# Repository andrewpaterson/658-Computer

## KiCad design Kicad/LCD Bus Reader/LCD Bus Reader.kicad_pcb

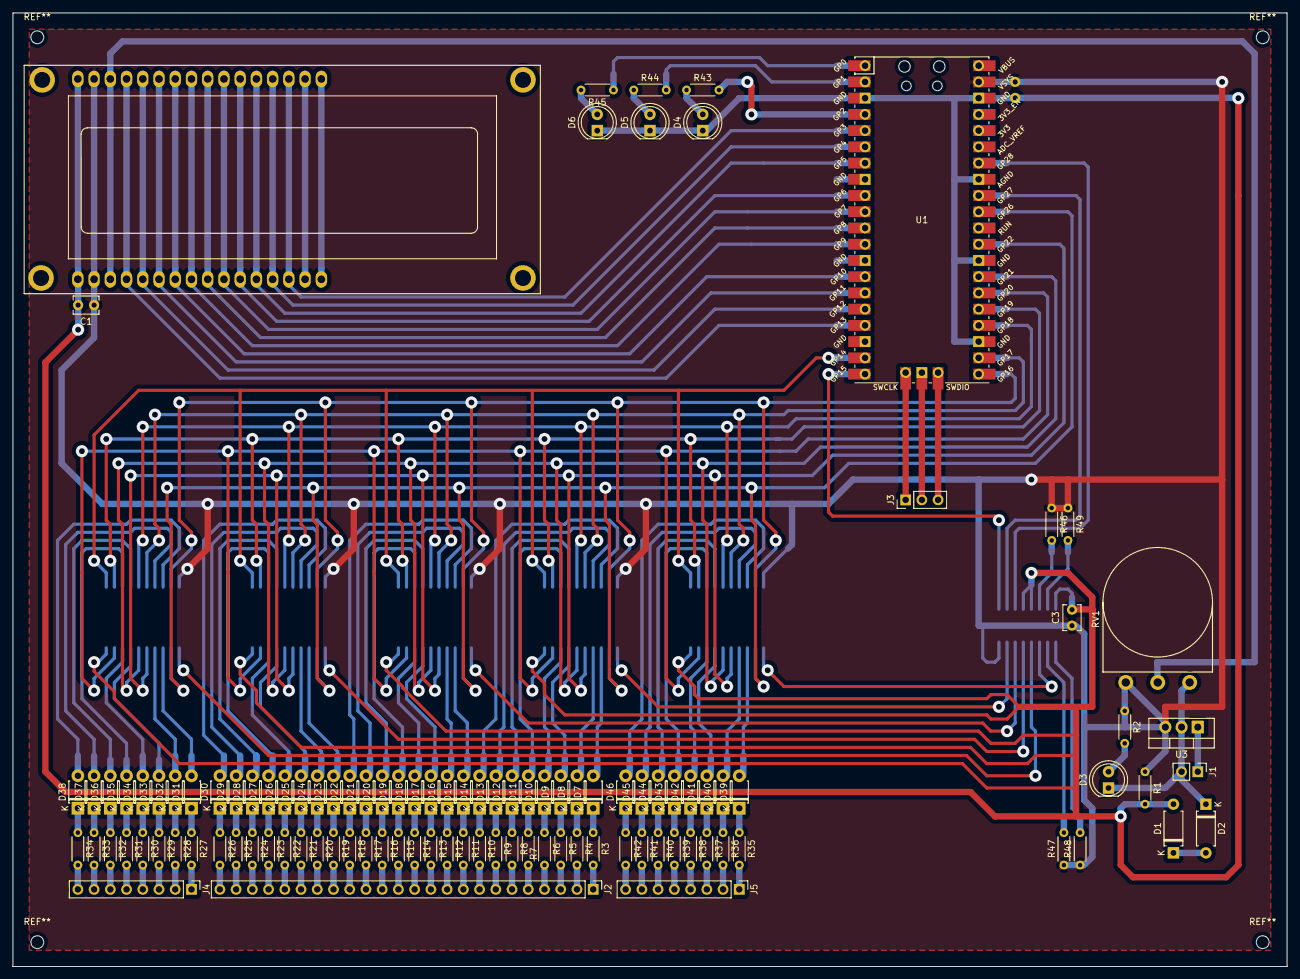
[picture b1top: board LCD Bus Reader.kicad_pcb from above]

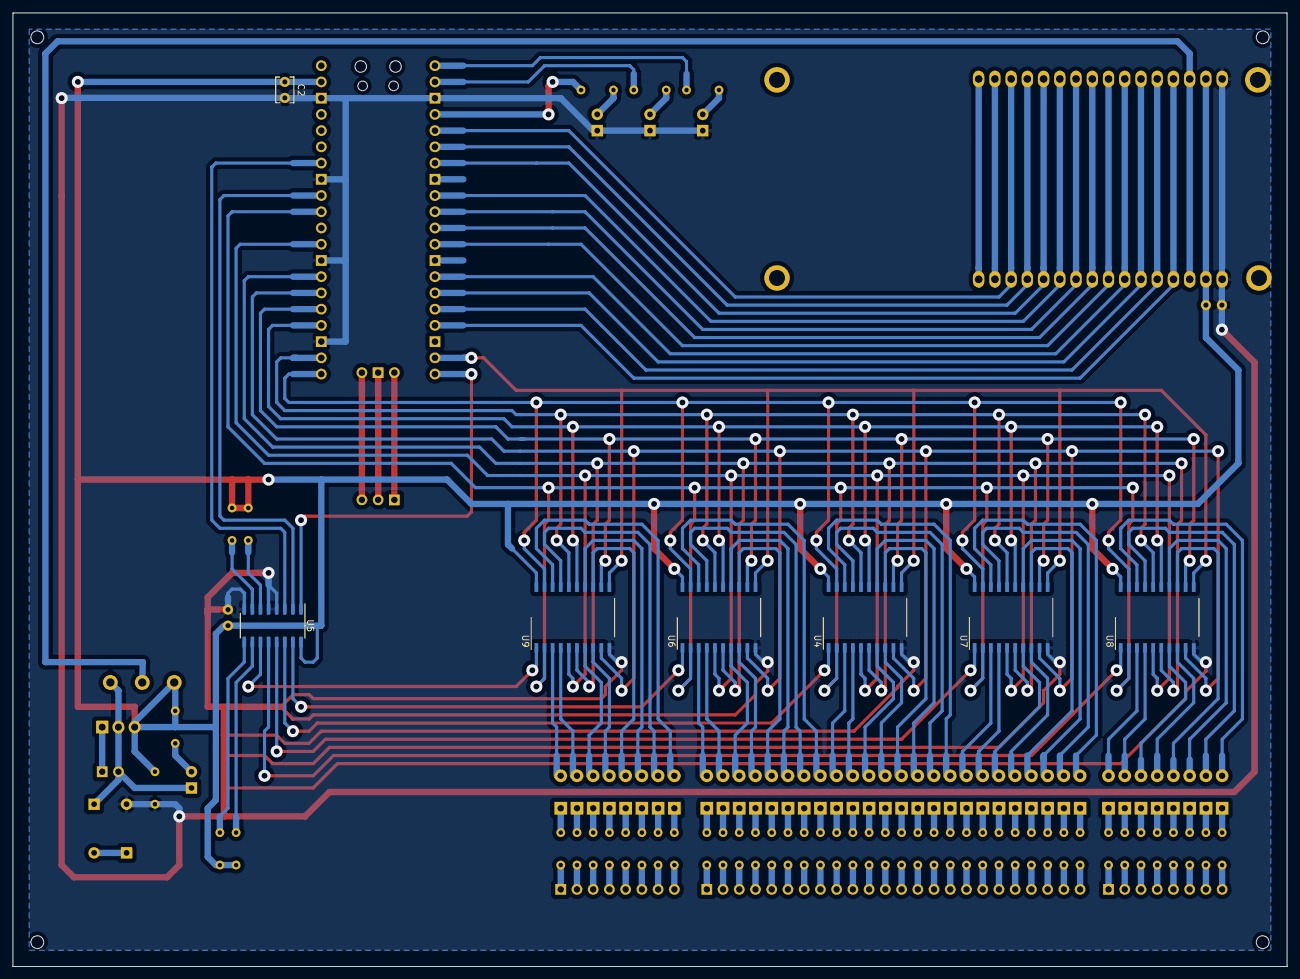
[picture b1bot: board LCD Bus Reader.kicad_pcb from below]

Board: 2 copper layers, 199.4 x 149.2 mm, 113 parts (7 on the bottom side), 168 nets.

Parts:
C1, C2, C3: C; C_Disc_D3.8mm_W2.6mm_P2.50mm
D1, D2: D_Zener; D_A-405_P7.62mm_Horizontal
D3, D4, D5, D6: LED; LED_D5.0mm
D7, D8, D9, D10, D11, D12, D13, D14, D15, D16, D17, D18, D19, D20, D21, D22, D23, D24, D25, D26, D27, D28, D29, D30, D31, D32, D33, D34, D35, D36, D37, D38, D39, D40, D41, D42, D43, D44, D45, D46: 1N4148; D_T-1_P5.08mm_Horizontal
J1: Conn_01x02_Male; PinHeader_1x02_P2.54mm_Vertical
J2: Conn_01x24_Male; PinHeader_1x24_P2.54mm_Vertical
J3: Conn_01x03_Male; PinHeader_1x03_P2.54mm_Vertical
J4, J5: Conn_01x08_Male; PinHeader_1x08_P2.54mm_Vertical
R1, R2, R3, R4, R5, R6, R7, R8, R9, R10, R11, R12, R13, R14, R15, R16, R17, R18, R19, R20, R21, R22, R23, R24, R25, R26, R27, R28, R29, R30, R31, R32, R33, R34, R35, R36, R37, R38, R39, R40, R41, R42, R43, R44, R45, R46, R47, R48, R49: R; R_Axial_DIN0204_L3.6mm_D1.6mm_P5.08mm_Horizontal
RV1: R_POT; Potentiometer_Omeg_PC16BU_Vertical
U1: Pico; RPi_Pico_SMD_TH
U2: RC1602A; NMTC-S16205
U3: L7805; TO-220-3_Vertical
U4, U6, U7, U8, U9: 74LS373; SO-20_12.8x7.5mm_P1.27mm
U5: 74LS138; SO-16_3.9x9.9mm_P1.27mm

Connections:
+12V: J1.1, U3.1
/0V: D2.1, D3.1, J1.2, RV1.1, U3.2
/1.6V: C1.2, C2.2, C3.2, D1.2, D4.1, D5.1, D6.1, R1.2, U1.3, U1.23, U1.28, U1.33, U1.38, U2.1, U4.10, U5.4, U5.5, U5.8, U6.10, U7.10, U8.10, U9.10
/5V: C1.1, C2.1, C3.1, R1.1, R2.1, R46.1, R47.1, R48.1, R49.1, RV1.3, U1.39, U2.2, U3.3, U4.20, U5.16, U6.20, U7.20, U8.20, U9.20
/CE0: U5.15, U6.1
/CE1: U4.1, U5.14
/CE2: U5.13, U7.1
/CE3: U5.12, U8.1
/CE4: U5.11, U9.1
/CE5: R47.2, U5.10
/CE6: R48.2, U5.9
/CE7: R49.2, U5.7
/CS0: U1.20, U5.1
/CS1: U1.32, U5.2
/CS2: U1.34, U5.3
/DB0: U1.14, U2.7
/DB1: U1.12, U2.8
/DB2: U1.11, U2.9
/DB3: U1.10, U2.10
/DB4: U1.9, U2.11
/DB5: U1.7, U2.12
/DB6: U1.6, U2.13
/DB7: U1.5, U2.14
/DET3: R46.2, U5.6
/E: U1.15, U2.6
/L0: U1.31, U4.2, U6.2, U7.2, U8.2, U9.2
/L1: U1.29, U4.5, U6.5, U7.5, U8.5, U9.5
/L2: U1.27, U4.6, U6.6, U7.6, U8.6, U9.6
/L3: U1.26, U4.9, U6.9, U7.9, U8.9, U9.9
/L4: U1.25, U4.12, U6.12, U7.12, U8.12, U9.12
/L5: U1.24, U4.15, U6.15, U7.15, U8.15, U9.15
/L6: U1.22, U4.16, U6.16, U7.16, U8.16, U9.16
/L7: U1.21, U4.19, U6.19, U7.19, U8.19, U9.19
/LE: U1.19, U4.11, U6.11, U7.11, U8.11, U9.11
/P1: D7.2, U6.3
/P2: D8.2, U6.4
/P3: D9.2, U6.7
/P4: D10.2, U6.8
/P5: D11.2, U6.13
/P6: D12.2, U6.14
/P7: D13.2, U6.17
/P8: D14.2, U6.18
/P9: D15.2, U4.3
/P10: D16.2, U4.4
/P11: D17.2, U4.7
/P12: D18.2, U4.8
/P13: D19.2, U4.13
/P14: D20.2, U4.14
/P15: D21.2, U4.17
/P16: D22.2, U4.18
/P17: D23.2, U7.3
/P18: D24.2, U7.4
/P19: D25.2, U7.7
/P20: D26.2, U7.8
/P21: D27.2, U7.13
/P22: D28.2, U7.14
/P23: D29.2, U7.17
/P24: D30.2, U7.18
/P25: D31.2, U8.3
/P26: D32.2, U8.4
/P27: D33.2, U8.7
/P28: D34.2, U8.8
/P29: D35.2, U8.13
/P30: D36.2, U8.14
/P31: D37.2, U8.17
/P32: D38.2, U8.18
/P33: D39.2, U9.3
/P34: D40.2, U9.4
/P35: D41.2, U9.7
/P36: D42.2, U9.8
/P37: D43.2, U9.13
/P38: D44.2, U9.14
/P39: D45.2, U9.17
/P40: D46.2, U9.18
/RS: U1.17, U2.4
/RW: U1.16, U2.5
/V0: RV1.2, U2.3
unnamed: D1.1, D2.2
unnamed: D3.2, R2.2
unnamed: D4.2, R43.1
unnamed: D5.2, R44.1
unnamed: D6.2, R45.2
unnamed: D7.1, R3.1
unnamed: D8.1, R4.1
unnamed: D9.1, R5.1
unnamed: D10.1, R6.1
unnamed: D11.1, R7.1
unnamed: D12.1, R8.1
unnamed: D13.1, R9.1
unnamed: D14.1, R10.1
unnamed: D15.1, R11.1
unnamed: D16.1, R12.1
unnamed: D17.1, R13.1
unnamed: D18.1, R14.1
unnamed: D19.1, R15.1
unnamed: D20.1, R16.1
unnamed: D21.1, R17.1
unnamed: D22.1, R18.1
unnamed: D23.1, R19.1
unnamed: D24.1, R20.1
unnamed: D25.1, R21.1
unnamed: D26.1, R22.1
unnamed: D27.1, R23.1
unnamed: D28.1, R24.1
unnamed: D29.1, R25.1
unnamed: D30.1, R26.1
unnamed: D31.1, R27.1
unnamed: D32.1, R28.1
unnamed: D33.1, R29.1
unnamed: D34.1, R30.1
unnamed: D35.1, R31.1
unnamed: D36.1, R32.1
unnamed: D37.1, R33.1
unnamed: D38.1, R34.1
unnamed: D39.1, R35.1
unnamed: D40.1, R36.1
unnamed: D41.1, R37.1
unnamed: D42.1, R38.1
unnamed: D43.1, R39.1
unnamed: D44.1, R40.1
unnamed: D45.1, R41.1
unnamed: D46.1, R42.1
unnamed: J2.1, R3.2
unnamed: J2.2, R4.2
unnamed: J2.3, R5.2
unnamed: J2.4, R6.2
unnamed: J2.5, R7.2
unnamed: J2.6, R8.2
unnamed: J2.7, R9.2
unnamed: J2.8, R10.2
unnamed: J2.9, R11.2
unnamed: J2.10, R12.2
unnamed: J2.11, R13.2
unnamed: J2.12, R14.2
unnamed: J2.13, R15.2
unnamed: J2.14, R16.2
unnamed: J2.15, R17.2
unnamed: J2.16, R18.2
unnamed: J2.17, R19.2
unnamed: J2.18, R20.2
unnamed: J2.19, R21.2
unnamed: J2.20, R22.2
unnamed: J2.21, R23.2
unnamed: J2.22, R24.2
unnamed: J2.23, R25.2
unnamed: J2.24, R26.2
unnamed: J3.1, U1.41
unnamed: J3.2, U1.42
unnamed: J3.3, U1.43
unnamed: J4.1, R27.2
unnamed: J4.2, R28.2
unnamed: J4.3, R29.2
unnamed: J4.4, R30.2
unnamed: J4.5, R31.2
unnamed: J4.6, R32.2
unnamed: J4.7, R33.2
unnamed: J4.8, R34.2
unnamed: J5.1, R35.2
unnamed: J5.2, R36.2
unnamed: J5.3, R37.2
unnamed: J5.4, R38.2
unnamed: J5.5, R39.2
unnamed: J5.6, R40.2
unnamed: J5.7, R41.2
unnamed: J5.8, R42.2
unnamed: R43.2, U1.4
unnamed: R44.2, U1.2
unnamed: R45.1, U1.1

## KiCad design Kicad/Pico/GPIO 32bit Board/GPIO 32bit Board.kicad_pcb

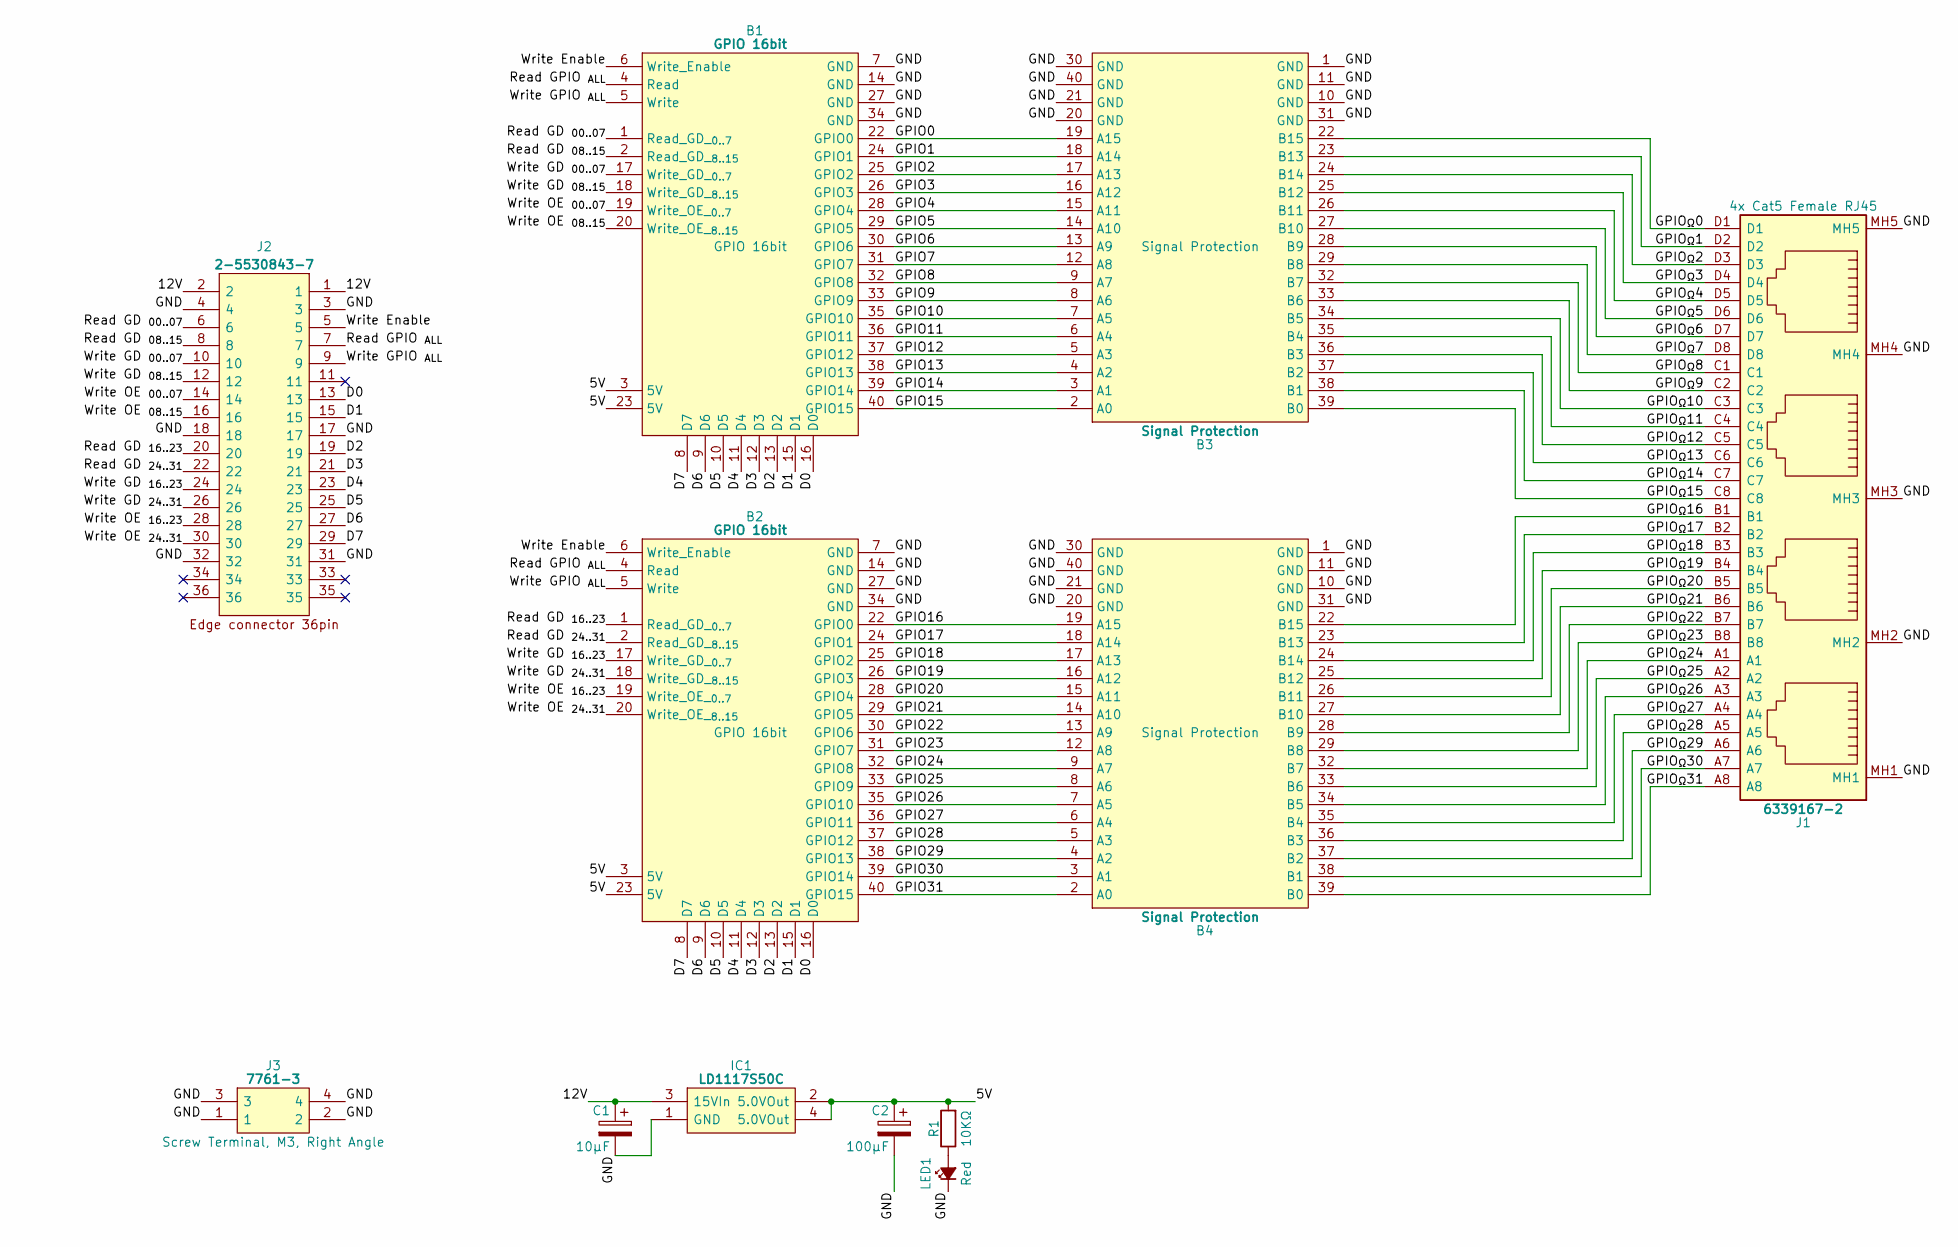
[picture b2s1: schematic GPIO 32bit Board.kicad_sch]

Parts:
B1, B2: GPIO 16bit; HCP65_GPIO_16bit
B3, B4: Signal Protection; HCP65_Signal_Protection
C1: 10μF; CP_Radial_D4.0mm_P2.00mm
C2: 100μF; CP_Radial_D4.0mm_P2.00mm
IC1: LD1117S50C; LD1117S33C; Manufacturer_Part_Number LD1117S50C
J1: 6339167-2; 63391672; Manufacturer_Part_Number 6339167-2; Mouser Part Number 571-6339167-2
J2: 2-5530843-7; 36pin Edge Connector; Manufacturer_Part_Number 2-5530843-7; Mouser Part Number 571-2-5530843-7
J3: 7761-3; 77613; Manufacturer_Part_Number 7761-3
LED1: Red; LED_D5.0mm
R1: 10KΩ; R_Axial_DIN0204_L3.6mm_D1.6mm_P5.08mm_Horizontal

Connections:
/5V: B1.3 (5V), B1.23 (5V), B2.3 (5V), B2.23 (5V), C2.1, IC1.2 (5.0VOut), IC1.4 (5.0VOut), R1.2
/12V: C1.1, IC1.3 (15VIn), J2.1, J2.2
/D0: B1.16 (D0), B2.16 (D0), J2.13
/D1: B1.15 (D1), B2.15 (D1), J2.15
/D2: B1.13 (D2), B2.13 (D2), J2.19
/D3: B1.12 (D3), B2.12 (D3), J2.21
/D4: B1.11 (D4), B2.11 (D4), J2.23
/D5: B1.10 (D5), B2.10 (D5), J2.25
/D6: B1.9 (D6), B2.9 (D6), J2.27
/D7: B1.8 (D7), B2.8 (D7), J2.29
/GND: B1.7 (GND), B1.14 (GND), B1.27 (GND), B1.34 (GND), B2.7 (GND), B2.14 (GND), B2.27 (GND), B2.34 (GND), B3.1 (GND), B3.10 (GND), B3.11 (GND), B3.20 (GND), B3.21 (GND), B3.30 (GND), B3.31 (GND), B3.40 (GND), B4.1 (GND), B4.10 (GND), B4.11 (GND), B4.20 (GND), B4.21 (GND), B4.30 (GND), B4.31 (GND), B4.40 (GND), C1.2, C2.2, IC1.1 (GND), J1.MH1, J1.MH2, J1.MH3, J1.MH4, J1.MH5, J2.3, J2.4, J2.17, J2.18, J2.31, J2.32, J3.1, J3.2, J3.3, J3.4, LED1.1 (K)
/GPIO0: B1.22 (GPIO0), B3.19 (A15)
/GPIO1: B1.24 (GPIO1), B3.18 (A14)
/GPIO2: B1.25 (GPIO2), B3.17 (A13)
/GPIO3: B1.26 (GPIO3), B3.16 (A12)
/GPIO4: B1.28 (GPIO4), B3.15 (A11)
/GPIO5: B1.29 (GPIO5), B3.14 (A10)
/GPIO6: B1.30 (GPIO6), B3.13 (A9)
/GPIO7: B1.31 (GPIO7), B3.12 (A8)
/GPIO8: B1.32 (GPIO8), B3.9 (A7)
/GPIO9: B1.33 (GPIO9), B3.8 (A6)
/GPIO10: B1.35 (GPIO10), B3.7 (A5)
/GPIO11: B1.36 (GPIO11), B3.6 (A4)
/GPIO12: B1.37 (GPIO12), B3.5 (A3)
/GPIO13: B1.38 (GPIO13), B3.4 (A2)
/GPIO14: B1.39 (GPIO14), B3.3 (A1)
/GPIO15: B1.40 (GPIO15), B3.2 (A0)
/GPIO16: B2.22 (GPIO0), B4.19 (A15)
/GPIO17: B2.24 (GPIO1), B4.18 (A14)
/GPIO18: B2.25 (GPIO2), B4.17 (A13)
/GPIO19: B2.26 (GPIO3), B4.16 (A12)
/GPIO20: B2.28 (GPIO4), B4.15 (A11)
/GPIO21: B2.29 (GPIO5), B4.14 (A10)
/GPIO22: B2.30 (GPIO6), B4.13 (A9)
/GPIO23: B2.31 (GPIO7), B4.12 (A8)
/GPIO24: B2.32 (GPIO8), B4.9 (A7)
/GPIO25: B2.33 (GPIO9), B4.8 (A6)
/GPIO26: B2.35 (GPIO10), B4.7 (A5)
/GPIO27: B2.36 (GPIO11), B4.6 (A4)
/GPIO28: B2.37 (GPIO12), B4.5 (A3)
/GPIO29: B2.38 (GPIO13), B4.4 (A2)
/GPIO30: B2.39 (GPIO14), B4.3 (A1)
/GPIO31: B2.40 (GPIO15), B4.2 (A0)
/GPIO_{Ω}0: B3.22 (B15), J1.D1
/GPIO_{Ω}1: B3.23 (B13), J1.D2
/GPIO_{Ω}2: B3.24 (B14), J1.D3
/GPIO_{Ω}3: B3.25 (B12), J1.D4
/GPIO_{Ω}4: B3.26 (B11), J1.D5
/GPIO_{Ω}5: B3.27 (B10), J1.D6
/GPIO_{Ω}6: B3.28 (B9), J1.D7
/GPIO_{Ω}7: B3.29 (B8), J1.D8
/GPIO_{Ω}8: B3.32 (B7), J1.C1
/GPIO_{Ω}9: B3.33 (B6), J1.C2
/GPIO_{Ω}10: B3.34 (B5), J1.C3
/GPIO_{Ω}11: B3.35 (B4), J1.C4
/GPIO_{Ω}12: B3.36 (B3), J1.C5
/GPIO_{Ω}13: B3.37 (B2), J1.C6
/GPIO_{Ω}14: B3.38 (B1), J1.C7
/GPIO_{Ω}15: B3.39 (B0), J1.C8
/GPIO_{Ω}16: B4.22 (B15), J1.B1
/GPIO_{Ω}17: B4.23 (B13), J1.B2
/GPIO_{Ω}18: B4.24 (B14), J1.B3
/GPIO_{Ω}19: B4.25 (B12), J1.B4
/GPIO_{Ω}20: B4.26 (B11), J1.B5
/GPIO_{Ω}21: B4.27 (B10), J1.B6
/GPIO_{Ω}22: B4.28 (B9), J1.B7
/GPIO_{Ω}23: B4.29 (B8), J1.B8
/GPIO_{Ω}24: B4.32 (B7), J1.A1
/GPIO_{Ω}25: B4.33 (B6), J1.A2
/GPIO_{Ω}26: B4.34 (B5), J1.A3
/GPIO_{Ω}27: B4.35 (B4), J1.A4
/GPIO_{Ω}28: B4.36 (B3), J1.A5
/GPIO_{Ω}29: B4.37 (B2), J1.A6
/GPIO_{Ω}30: B4.38 (B1), J1.A7
/GPIO_{Ω}31: B4.39 (B0), J1.A8
/Read GD _{00..07}: B1.1 (Read_GD__{0..7}), J2.6
/Read GD _{08..15}: B1.2 (Read_GD__{8..15}), J2.8
/Read GD _{16..23}: B2.1 (Read_GD__{0..7}), J2.20
/Read GD _{24..31}: B2.2 (Read_GD__{8..15}), J2.22
/Read GPIO _{ALL}: B1.4 (Read), B2.4 (Read), J2.7
/Write Enable: B1.6 (Write_Enable), B2.6 (Write_Enable), J2.5
/Write GD _{00..07}: B1.17 (Write_GD__{0..7}), J2.10
/Write GD _{08..15}: B1.18 (Write_GD__{8..15}), J2.12
/Write GD _{16..23}: B2.17 (Write_GD__{0..7}), J2.24
/Write GD _{24..31}: B2.18 (Write_GD__{8..15}), J2.26
/Write GPIO _{ALL}: B1.5 (Write), B2.5 (Write), J2.9
/Write OE _{00..07}: B1.19 (Write_OE__{0..7}), J2.14
/Write OE _{08..15}: B1.20 (Write_OE__{8..15}), J2.16
/Write OE _{16..23}: B2.19 (Write_OE__{0..7}), J2.28
/Write OE _{24..31}: B2.20 (Write_OE__{8..15}), J2.30
unnamed: LED1.2 (A), R1.1

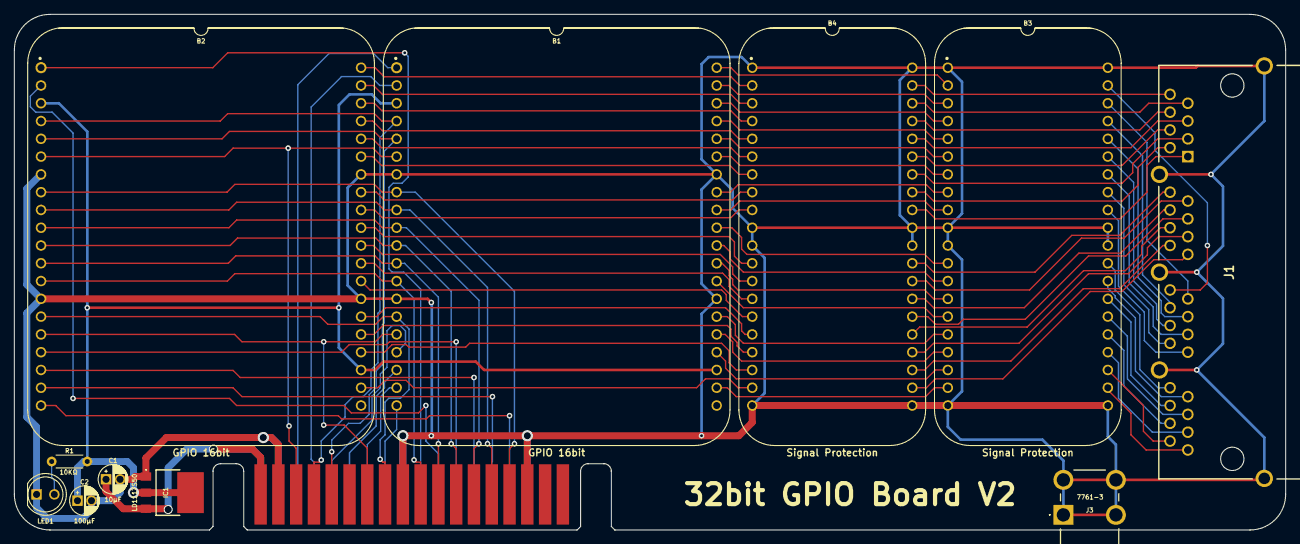
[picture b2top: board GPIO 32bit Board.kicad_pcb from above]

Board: 2 copper layers, 181.6 x 73.7 mm, 12 parts (0 on the bottom side), 91 nets.

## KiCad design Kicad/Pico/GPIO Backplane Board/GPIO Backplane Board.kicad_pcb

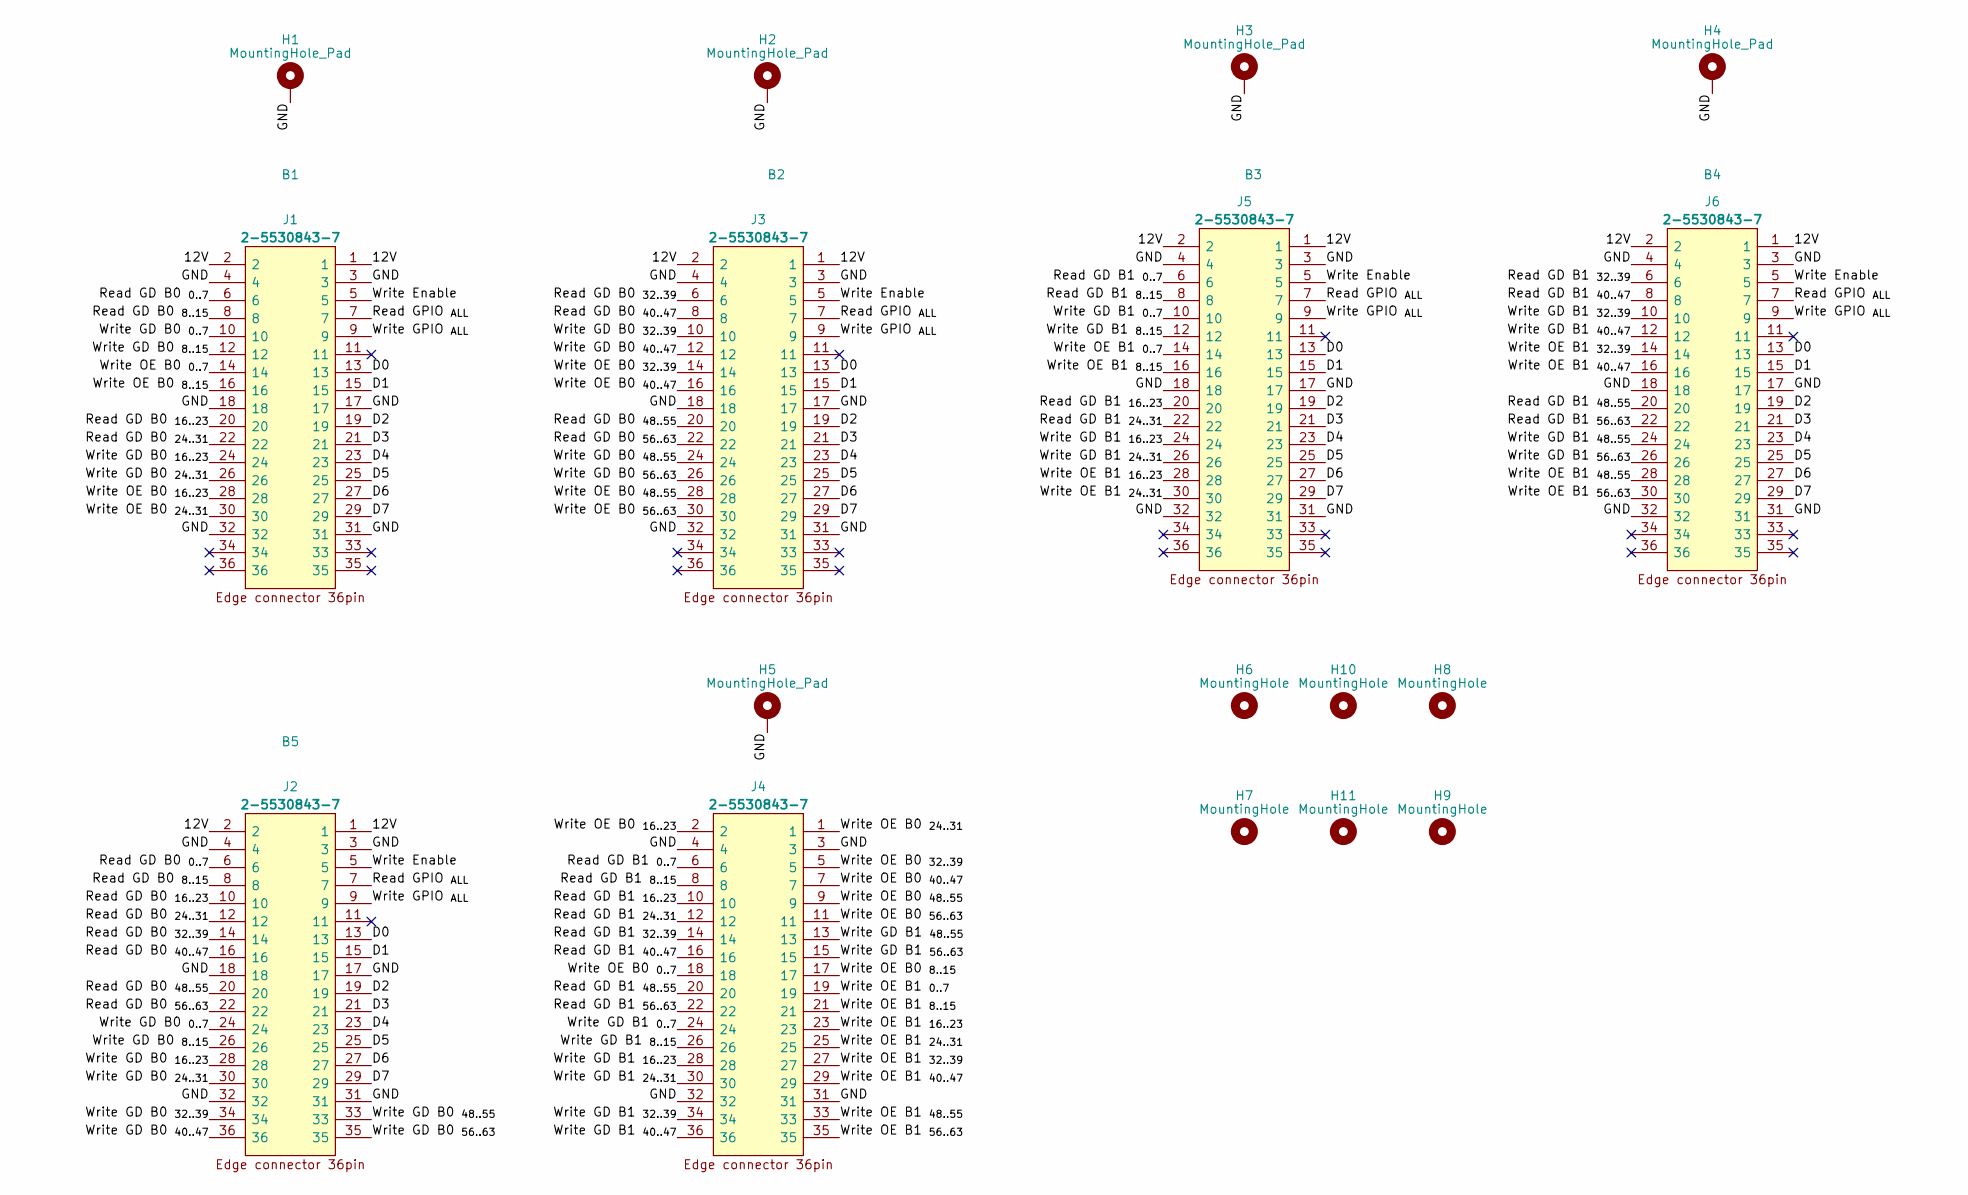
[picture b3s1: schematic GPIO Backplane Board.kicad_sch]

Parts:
B1, B2, B3, B4: HCP65_GPIO_32bit_Board
B5: HCP65_GPIO_Controller_Board
H1, H2, H3, H4, H5: MountingHole_Pad; MountingHole_3.2mm_M3_Pad
H6, H7, H8, H9, H10, H11: MountingHole; MountingHole_3.2mm_M3
J1, J2, J3, J4, J5, J6: 2-5530843-7; 255308437; Manufacturer_Part_Number 2-5530843-7; Mouser Part Number 571-2-5530843-7

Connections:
/12V: J1.1, J1.2, J2.1, J2.2, J3.1, J3.2, J5.1, J5.2, J6.1, J6.2
/D0: J1.13, J2.13, J3.13, J5.13, J6.13
/D1: J1.15, J2.15, J3.15, J5.15, J6.15
/D2: J1.19, J2.19, J3.19, J5.19, J6.19
/D3: J1.21, J2.21, J3.21, J5.21, J6.21
/D4: J1.23, J2.23, J3.23, J5.23, J6.23
/D5: J1.25, J2.25, J3.25, J5.25, J6.25
/D6: J1.27, J2.27, J3.27, J5.27, J6.27
/D7: J1.29, J2.29, J3.29, J5.29, J6.29
/GND: H1.1, H2.1, H3.1, H4.1, H5.1, J1.3, J1.4, J1.17, J1.18, J1.31, J1.32, J2.3, J2.4, J2.17, J2.18, J2.31, J2.32, J3.3, J3.4, J3.17, J3.18, J3.31, J3.32, J4.3, J4.4, J4.31, J4.32, J5.3, J5.4, J5.17, J5.18, J5.31, J5.32, J6.3, J6.4, J6.17, J6.18, J6.31, J6.32
/Read GD B0 _{0..7}: J1.6, J2.6
/Read GD B0 _{8..15}: J1.8, J2.8
/Read GD B0 _{16..23}: J1.20, J2.10
/Read GD B0 _{24..31}: J1.22, J2.12
/Read GD B0 _{32..39}: J2.14, J3.6
/Read GD B0 _{40..47}: J2.16, J3.8
/Read GD B0 _{48..55}: J2.20, J3.20
/Read GD B0 _{56..63}: J2.22, J3.22
/Read GD B1 _{0..7}: J4.6, J5.6
/Read GD B1 _{8..15}: J4.8, J5.8
/Read GD B1 _{16..23}: J4.10, J5.20
/Read GD B1 _{24..31}: J4.12, J5.22
/Read GD B1 _{32..39}: J4.14, J6.6
/Read GD B1 _{40..47}: J4.16, J6.8
/Read GD B1 _{48..55}: J4.20, J6.20
/Read GD B1 _{56..63}: J4.22, J6.22
/Read GPIO _{ALL}: J1.7, J2.7, J3.7, J5.7, J6.7
/Write Enable: J1.5, J2.5, J3.5, J5.5, J6.5
/Write GD B0 _{0..7}: J1.10, J2.24
/Write GD B0 _{8..15}: J1.12, J2.26
/Write GD B0 _{16..23}: J1.24, J2.28
/Write GD B0 _{24..31}: J1.26, J2.30
/Write GD B0 _{32..39}: J2.34, J3.10
/Write GD B0 _{40..47}: J2.36, J3.12
/Write GD B0 _{48..55}: J2.33, J3.24
/Write GD B0 _{56..63}: J2.35, J3.26
/Write GD B1 _{0..7}: J4.24, J5.10
/Write GD B1 _{8..15}: J4.26, J5.12
/Write GD B1 _{16..23}: J4.28, J5.24
/Write GD B1 _{24..31}: J4.30, J5.26
/Write GD B1 _{32..39}: J4.34, J6.10
/Write GD B1 _{40..47}: J4.36, J6.12
/Write GD B1 _{48..55}: J4.13, J6.24
/Write GD B1 _{56..63}: J4.15, J6.26
/Write GPIO _{ALL}: J1.9, J2.9, J3.9, J5.9, J6.9
/Write OE B0 _{0..7}: J1.14, J4.18
/Write OE B0 _{8..15}: J1.16, J4.17
/Write OE B0 _{16..23}: J1.28, J4.2
/Write OE B0 _{24..31}: J1.30, J4.1
/Write OE B0 _{32..39}: J3.14, J4.5
/Write OE B0 _{40..47}: J3.16, J4.7
/Write OE B0 _{48..55}: J3.28, J4.9
/Write OE B0 _{56..63}: J3.30, J4.11
/Write OE B1 _{0..7}: J4.19, J5.14
/Write OE B1 _{8..15}: J4.21, J5.16
/Write OE B1 _{16..23}: J4.23, J5.28
/Write OE B1 _{24..31}: J4.25, J5.30
/Write OE B1 _{32..39}: J4.27, J6.14
/Write OE B1 _{40..47}: J4.29, J6.16
/Write OE B1 _{48..55}: J4.33, J6.28
/Write OE B1 _{56..63}: J4.35, J6.30

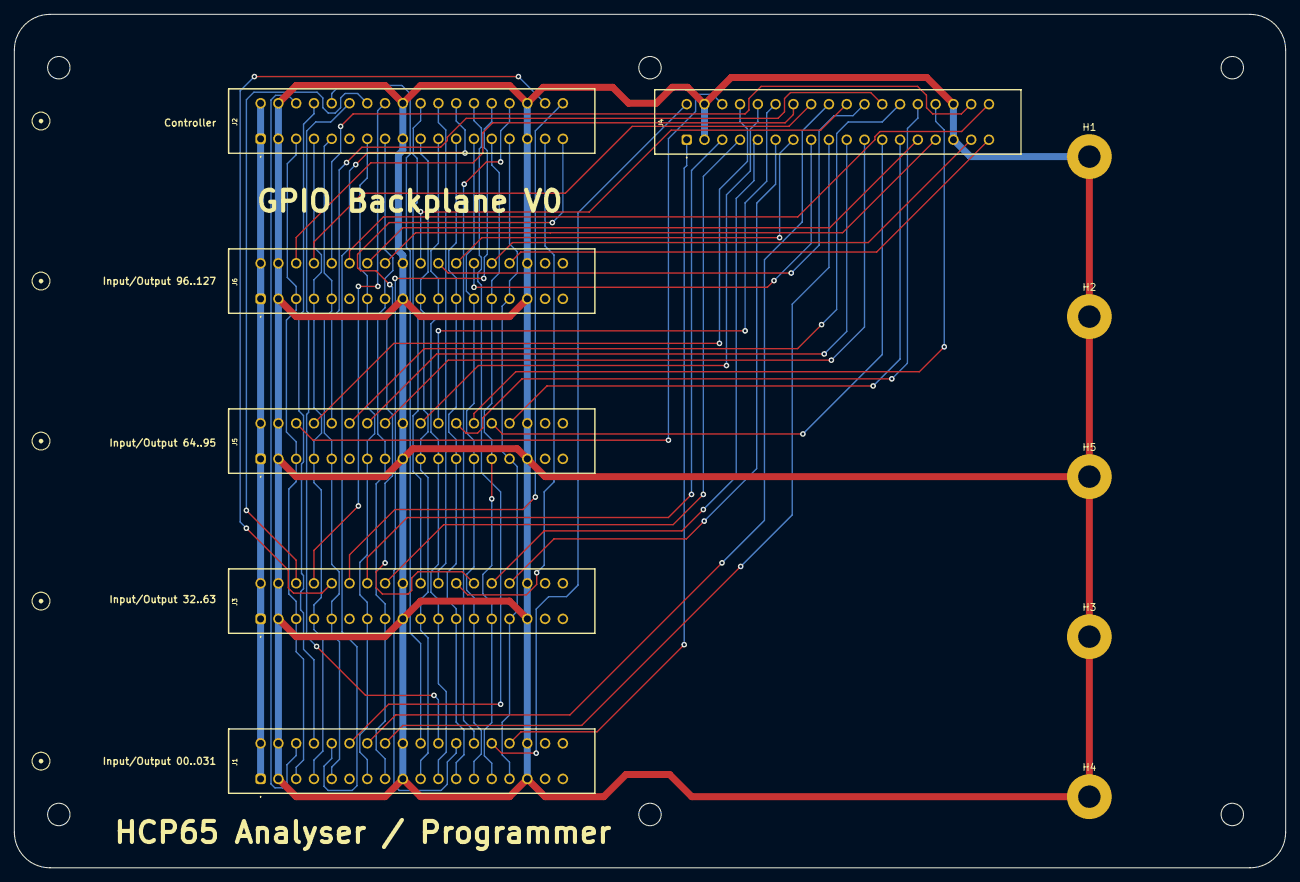
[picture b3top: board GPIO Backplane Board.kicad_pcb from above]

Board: 2 copper layers, 181.6 x 121.9 mm, 22 parts (0 on the bottom side), 61 nets.

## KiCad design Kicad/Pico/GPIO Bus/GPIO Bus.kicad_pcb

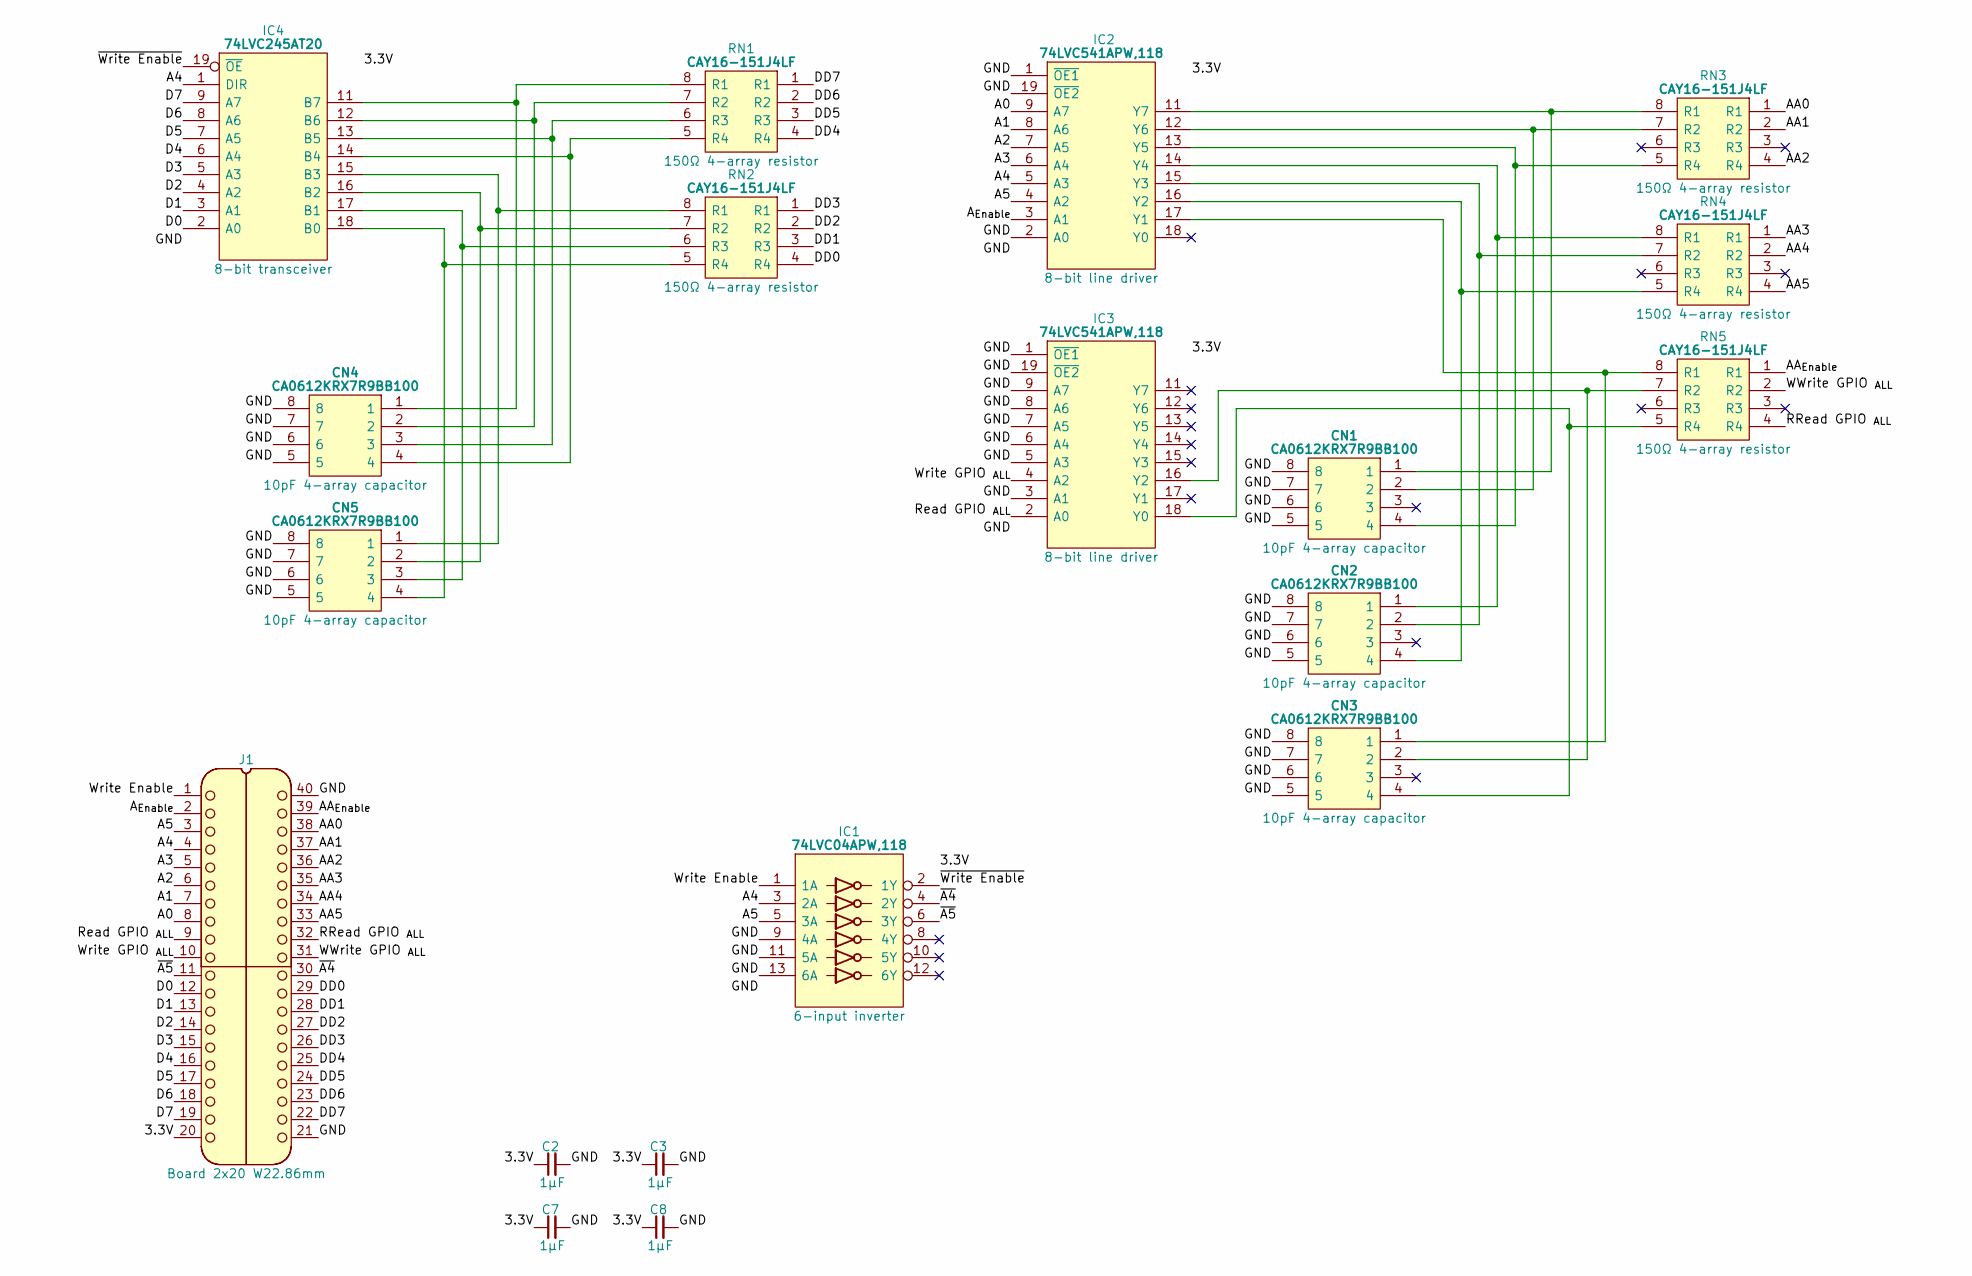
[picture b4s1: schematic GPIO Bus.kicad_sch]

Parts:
C2, C3, C7, C8: 1μF; C_0805
CN1, CN2, CN3, CN4, CN5: CA0612KRX7R9BB100; Manufacturer_Part_Number CA0612KRX7R9BB102; Mouser Part Number 603-CA612KRX7R9BB102
IC1: 74LVC04APW,118; SOP65P640X110-14N; Manufacturer_Part_Number 74LVC04APW,118; Mouser Part Number 771-74LVC04APW-T
IC2, IC3: 74LVC541APW,118; SOP65P640X110-20N; Mouser Part Number 771-74LVC541APW-T
IC4: 74LVC245AT20; SOP65P640X120-20N; Manufacturer_Part_Number 74LVC245AT20-13; Mouser Part Number 621-74LVC245AT20-13
J1: Board 2x20 W22.86mm; DIP-40_Board_W22.86mm
RN1, RN2, RN3, RN4, RN5: CAY16-151J4LF; CAY16-J4; Manufacturer_Part_Number CAY16-151J4LF; Mouser Part Number 652-CAY16-151J4LF

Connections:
/3.3V: C2.1, C3.1, C7.1, C8.1, IC1.14 (3V), IC2.20 (3V), IC3.20 (3V), IC4.20 (3V), J1.20
/A0: IC2.9 (A7), J1.8
/A1: IC2.8 (A6), J1.7
/A2: IC2.7 (A5), J1.6
/A3: IC2.6 (A4), J1.5
/A4: IC1.3 (2A), IC2.5 (A3), IC4.1 (DIR), J1.4
/A5: IC1.5 (3A), IC2.4 (A2), J1.3
/AA0: J1.38, RN3.1 (R1)
/AA1: J1.37, RN3.2 (R2)
/AA2: J1.36, RN3.4 (R4)
/AA3: J1.35, RN4.1 (R1)
/AA4: J1.34, RN4.2 (R2)
/AA5: J1.33, RN4.4 (R4)
/AA_{Enable}: J1.39, RN5.1 (R1)
/A_{Enable}: IC2.3 (A1), J1.2
/D0: IC4.2 (A0), J1.12
/D1: IC4.3 (A1), J1.13
/D2: IC4.4 (A2), J1.14
/D3: IC4.5 (A3), J1.15
/D4: IC4.6 (A4), J1.16
/D5: IC4.7 (A5), J1.17
/D6: IC4.8 (A6), J1.18
/D7: IC4.9 (A7), J1.19
/DD0: J1.29, RN2.4 (R4)
/DD1: J1.28, RN2.3 (R3)
/DD2: J1.27, RN2.2 (R2)
/DD3: J1.26, RN2.1 (R1)
/DD4: J1.25, RN1.4 (R4)
/DD5: J1.24, RN1.3 (R3)
/DD6: J1.23, RN1.2 (R2)
/DD7: J1.22, RN1.1 (R1)
/GND: C2.2, C3.2, C7.2, C8.2, CN1.5, CN1.6, CN1.7, CN1.8, CN2.5, CN2.6, CN2.7, CN2.8, CN3.5, CN3.6, CN3.7, CN3.8, CN4.5, CN4.6, CN4.7, CN4.8, CN5.5, CN5.6, CN5.7, CN5.8, IC1.7 (GND), IC1.9 (4A), IC1.11 (5A), IC1.13 (6A), IC2.1 (~OE1), IC2.2 (A0), IC2.10 (GND), IC2.19 (~OE2), IC3.1 (~OE1), IC3.3 (A1), IC3.5 (A3), IC3.6 (A4), IC3.7 (A5), IC3.8 (A6), IC3.9 (A7), IC3.10 (GND), IC3.19 (~OE2), IC4.10 (GND), J1.21, J1.40
/RRead GPIO _{ALL}: J1.32, RN5.4 (R4)
/Read GPIO _{ALL}: IC3.2 (A0), J1.9
/WWrite GPIO _{ALL}: J1.31, RN5.2 (R2)
/Write Enable: IC1.1 (1A), J1.1
/Write GPIO _{ALL}: IC3.4 (A2), J1.10
/~A4: IC1.4 (2Y), J1.30
/~A5: IC1.6 (3Y), J1.11
/~Write Enable: IC1.2 (1Y), IC4.19 (~OE)
unnamed: CN3.1, IC2.17 (Y1), RN5.8 (R1)
unnamed: CN2.4, IC2.16 (Y2), RN4.5 (R4)
unnamed: CN2.2, IC2.15 (Y3), RN4.7 (R2)
unnamed: CN2.1, IC2.14 (Y4), RN4.8 (R1)
unnamed: CN1.4, IC2.13 (Y5), RN3.5 (R4)
unnamed: CN1.2, IC2.12 (Y6), RN3.7 (R2)
unnamed: CN1.1, IC2.11 (Y7), RN3.8 (R1)
unnamed: CN3.4, IC3.18 (Y0), RN5.5 (R4)
unnamed: CN3.2, IC3.16 (Y2), RN5.7 (R2)
unnamed: CN5.4, IC4.18 (B0), RN2.5 (R4)
unnamed: CN5.3, IC4.17 (B1), RN2.6 (R3)
unnamed: CN5.2, IC4.16 (B2), RN2.7 (R2)
unnamed: CN5.1, IC4.15 (B3), RN2.8 (R1)
unnamed: CN4.4, IC4.14 (B4), RN1.5 (R4)
unnamed: CN4.3, IC4.13 (B5), RN1.6 (R3)
unnamed: CN4.2, IC4.12 (B6), RN1.7 (R2)
unnamed: CN4.1, IC4.11 (B7), RN1.8 (R1)

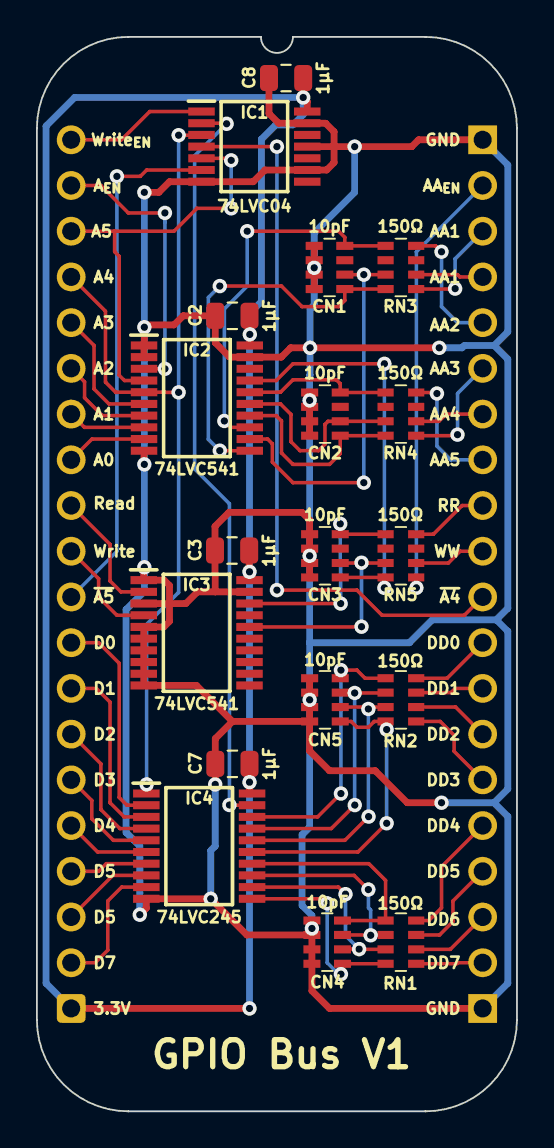
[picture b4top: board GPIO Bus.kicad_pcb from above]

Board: 2 copper layers, 26.7 x 59.7 mm, 19 parts (0 on the bottom side), 57 nets.
